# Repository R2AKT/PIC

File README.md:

License addendum - https://github.com/R2AKT/PIC/blob/main/Addendum.txt
# PIC
Programmable Interrupt Contoller (PIC) module. For connection to the CPU_8080 processor board - https://github.com/R2AKT/CPU_8080.

Status: in production for testing

Модуль программируемого контроллера прерываний (PIC). Для подключения к процессорной плате CPU_8080 - https://github.com/R2AKT/CPU_8080.

На базе часов реального времени для РАДИО-86РК.

Статус: в изготовлении для тестирования.

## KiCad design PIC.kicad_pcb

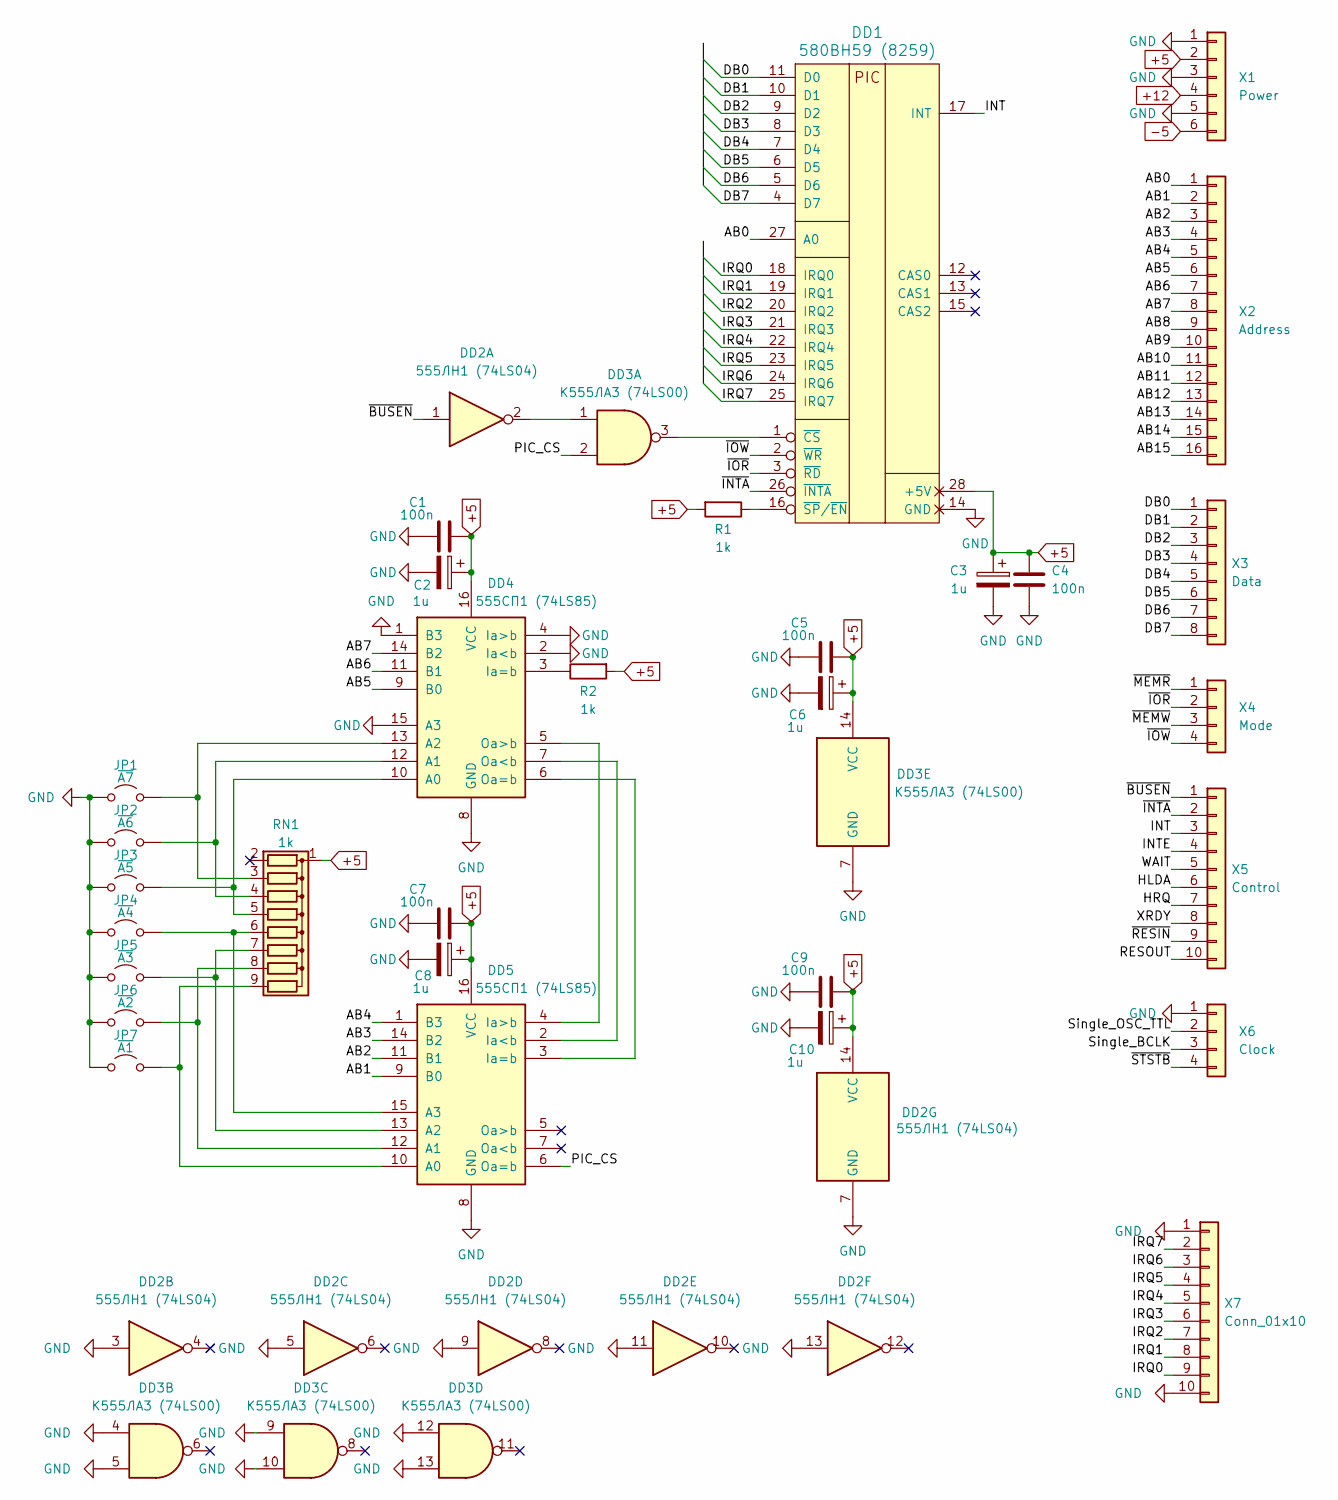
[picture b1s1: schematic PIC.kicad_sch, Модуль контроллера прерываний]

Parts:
C1, C4, C5, C7, C9: 100n; C_0805_2012Metric_Pad1.18x1.45mm_HandSolder
C2, C3, C6, C8, C10: 1u; CP_EIA-3216-18_Kemet-A_Pad1.58x1.35mm_HandSolder
DD1: 580ВН59 (8259); DIP-28_W15.24mm_Socket_LongPads
DD2: 555ЛН1 (74LS04); DIP-14_W7.62mm_Socket_LongPads
DD3: К555ЛА3 (74LS00); DIP-14_W7.62mm_Socket_LongPads
DD4, DD5: 555СП1 (74LS85); DIP-16_W7.62mm_Socket_LongPads
JP1: ~{A7}; SolderJumper-2_P1.3mm_Open_RoundedPad1.0x1.5mm
JP2: ~{A6}; SolderJumper-2_P1.3mm_Open_RoundedPad1.0x1.5mm
JP3: ~{A5}; SolderJumper-2_P1.3mm_Open_RoundedPad1.0x1.5mm
JP4: ~{A4}; SolderJumper-2_P1.3mm_Open_RoundedPad1.0x1.5mm
JP5: ~{A3}; SolderJumper-2_P1.3mm_Open_RoundedPad1.0x1.5mm
JP6: ~{A2}; SolderJumper-2_P1.3mm_Open_RoundedPad1.0x1.5mm
JP7: ~{A1}; SolderJumper-2_P1.3mm_Open_RoundedPad1.0x1.5mm
R1, R2: 1k; R_0805_2012Metric_Pad1.20x1.40mm_HandSolder
RN1: 1k; R_Array_SIP9
X1: Power; PinHeader_1x06_P2.54mm_Vertical
X2: Address; PinHeader_1x16_P2.54mm_Vertical
X3: Data; PinHeader_1x08_P2.54mm_Vertical
X4: Mode; PinHeader_1x04_P2.54mm_Vertical
X5: Control; PinHeader_1x10_P2.54mm_Vertical
X6: Clock; PinHeader_1x04_P2.54mm_Vertical
X7: Conn_01x10; PinHeader_1x10_P2.54mm_Vertical

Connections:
+5: C1.1, C2.1, C3.1, C4.1, C5.1, C6.1, C7.1, C8.1, C9.1, C10.1, DD1.28 (+5V), DD2.14 (VCC), DD3.14 (VCC), DD4.16 (VCC), DD5.16 (VCC), R1.2, R2.2, RN1.1 (common), X1.2
+12: X1.4
-5: X1.6
/AB0: DD1.27 (A0), X2.1
/AB1: DD5.9 (B0), X2.2
/AB2: DD5.11 (B1), X2.3
/AB3: DD5.14 (B2), X2.4
/AB4: DD5.1 (B3), X2.5
/AB5: DD4.9 (B0), X2.6
/AB6: DD4.11 (B1), X2.7
/AB7: DD4.14 (B2), X2.8
/AB8: X2.9
/AB9: X2.10
/AB10: X2.11
/AB11: X2.12
/AB12: X2.13
/AB13: X2.14
/AB14: X2.15
/AB15: X2.16
/DB0: DD1.11 (D0), X3.1
/DB1: DD1.10 (D1), X3.2
/DB2: DD1.9 (D2), X3.3
/DB3: DD1.8 (D3), X3.4
/DB4: DD1.7 (D4), X3.5
/DB5: DD1.6 (D5), X3.6
/DB6: DD1.5 (D6), X3.7
/DB7: DD1.4 (D7), X3.8
/HLDA: X5.6
/HRQ: X5.7
/INT: DD1.17 (INT), X5.3
/INTE: X5.4
/IRQ0: DD1.18 (IRQ0), X7.9
/IRQ1: DD1.19 (IRQ1), X7.8
/IRQ2: DD1.20 (IRQ2), X7.7
/IRQ3: DD1.21 (IRQ3), X7.6
/IRQ4: DD1.22 (IRQ4), X7.5
/IRQ5: DD1.23 (IRQ5), X7.4
/IRQ6: DD1.24 (IRQ6), X7.3
/IRQ7: DD1.25 (IRQ7), X7.2
/PIC_CS: DD3.2, DD5.6 (Oa=b)
/RESOUT: X5.10
/Single_BCLK: X6.3
/Single_OSC_TTL: X6.2
/WAIT: X5.5
/XRDY: X5.8
/~BUSEN: DD2.1, X5.1
/~INTA: DD1.26 (~INTA), X5.2
/~IOR: DD1.3 (~RD), X4.2
/~IOW: DD1.2 (~WR), X4.4
/~MEMR: X4.1
/~MEMW: X4.3
/~RESIN: X5.9
/~STSTB: X6.4
GND: C1.2, C2.2, C3.2, C4.2, C5.2, C6.2, C7.2, C8.2, C9.2, C10.2, DD1.14 (GND), DD2.3, DD2.5, DD2.7 (GND), DD2.9, DD2.11, DD2.13, DD3.4, DD3.5, DD3.7 (GND), DD3.9, DD3.10, DD3.12, DD3.13, DD4.1 (B3), DD4.2 (Ia<b), DD4.4 (Ia>b), DD4.8 (GND), DD4.15 (A3), DD5.8 (GND), JP1.1 (A), JP2.1 (A), JP3.1 (A), JP4.1 (A), JP5.1 (A), JP6.1 (A), JP7.1 (A), X1.1, X1.3, X1.5, X6.1, X7.1, X7.10
unnamed: DD1.1 (~CS), DD3.3
unnamed: DD1.16 (~SP/~EN), R1.1
unnamed: DD2.2, DD3.1
unnamed: DD4.10 (A0), JP3.2 (B), RN1.5 (R4)
unnamed: DD4.12 (A1), JP2.2 (B), RN1.4 (R3)
unnamed: DD4.13 (A2), JP1.2 (B), RN1.3 (R2)
unnamed: DD4.3 (Ia=b), R2.1
unnamed: DD4.7 (Oa<b), DD5.2 (Ia<b)
unnamed: DD4.6 (Oa=b), DD5.3 (Ia=b)
unnamed: DD4.5 (Oa>b), DD5.4 (Ia>b)
unnamed: DD5.10 (A0), JP7.2 (B), RN1.9 (R8)
unnamed: DD5.12 (A1), JP6.2 (B), RN1.8 (R7)
unnamed: DD5.13 (A2), JP5.2 (B), RN1.7 (R6)
unnamed: DD5.15 (A3), JP4.2 (B), RN1.6 (R5)

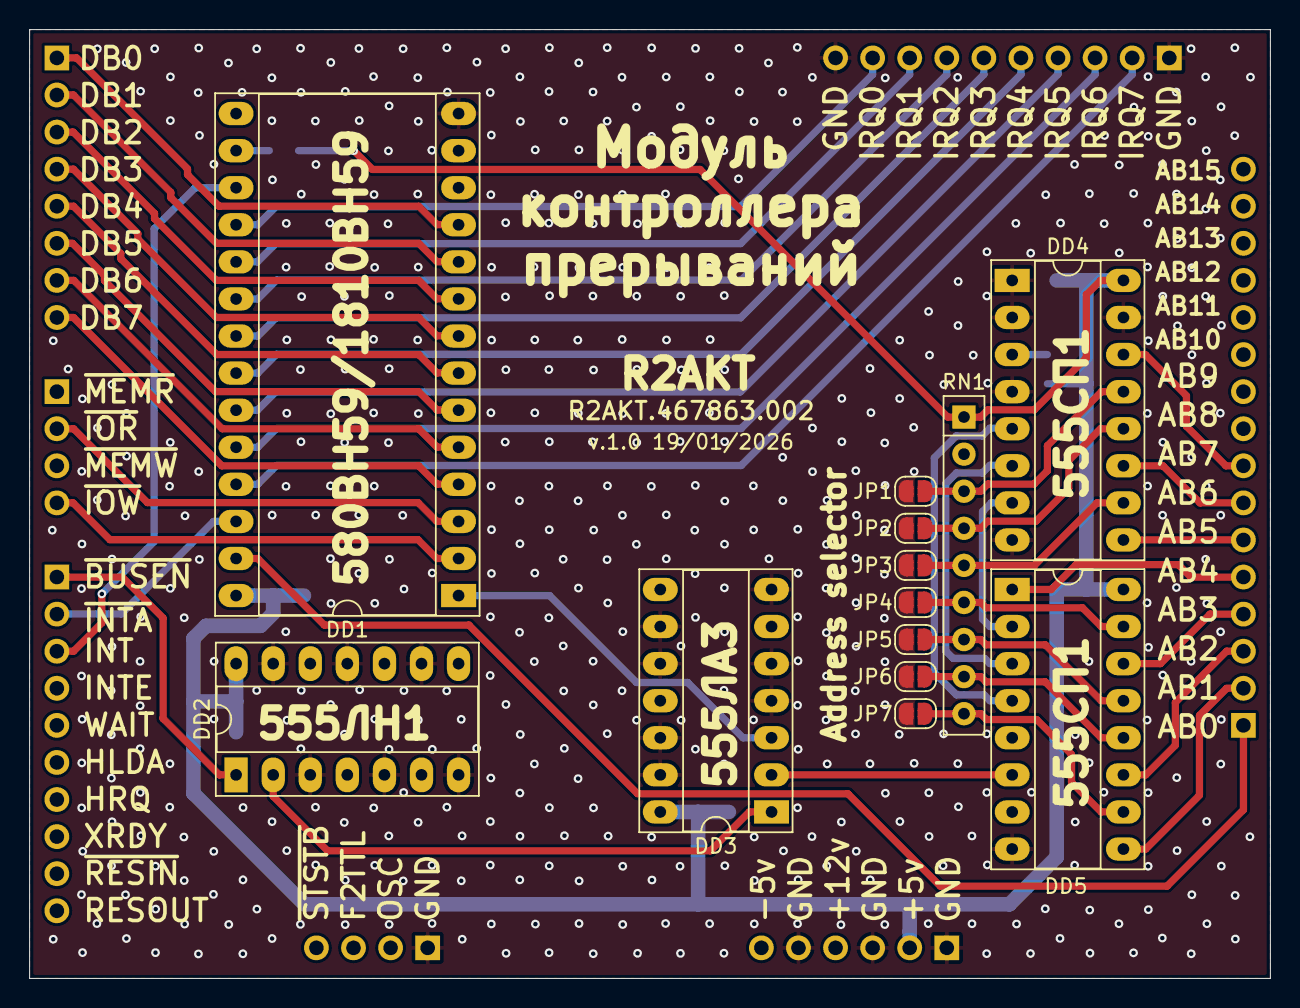
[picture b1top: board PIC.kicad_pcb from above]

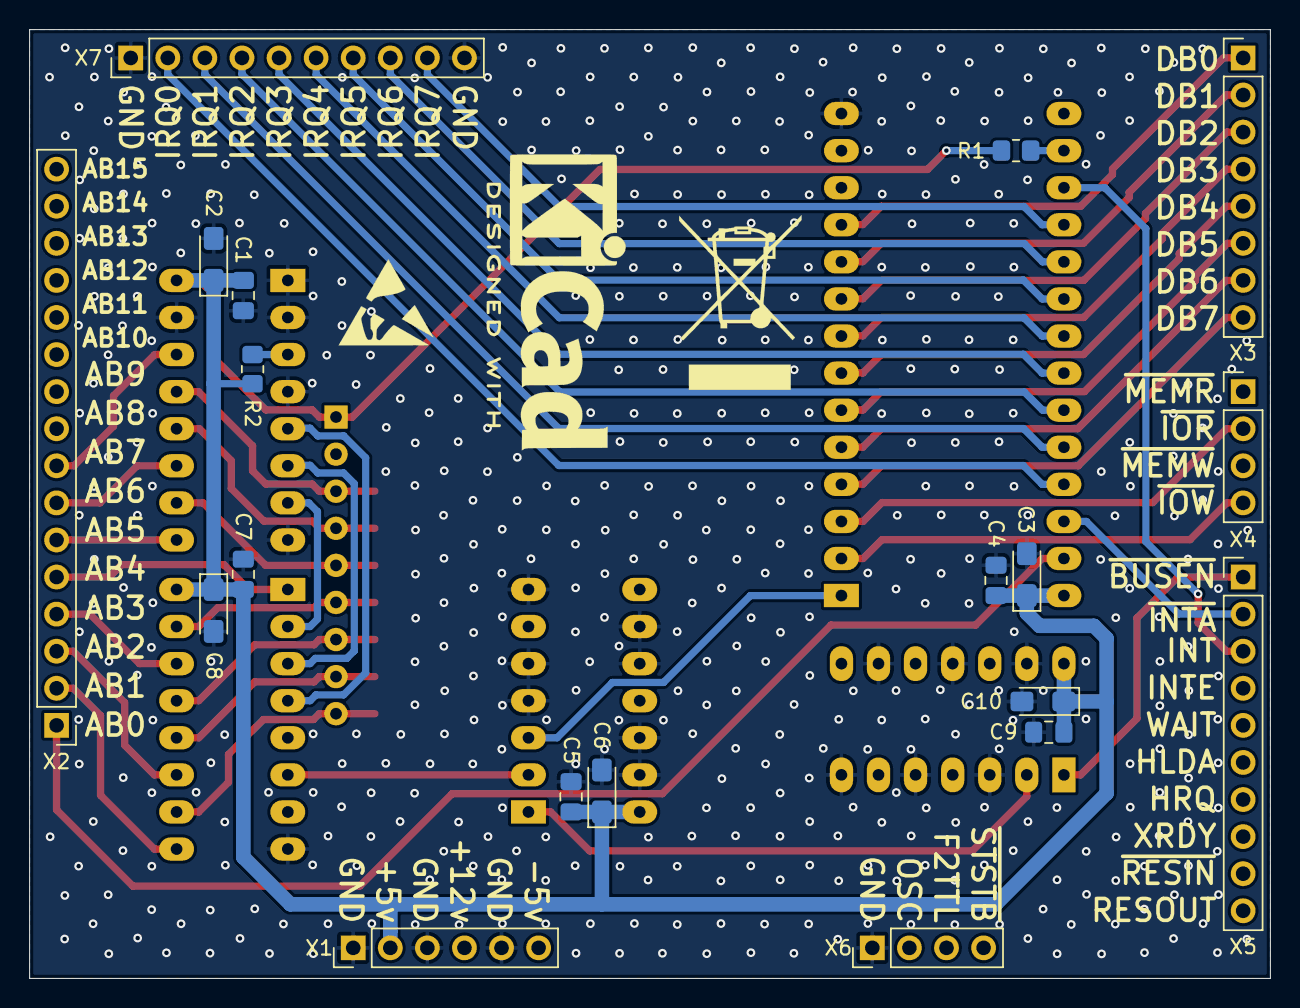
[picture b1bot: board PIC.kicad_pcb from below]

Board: 2 copper layers, 85.0 x 65.0 mm, 32 parts (19 on the bottom side), 46 nets.

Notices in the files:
README.md:
License: MIT
